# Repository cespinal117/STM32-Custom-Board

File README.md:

# STM32-Custom-Board

This is a board I decided to create to practice my PCB Design skills.  

I chose the STM32 as the main MCU due to me wanting to learn the STM32 platform.

My main motivation for the features of this board is that throughout college I mostly worked on projects involved Servo motors. Instead of having a separate Servo driver board with more wires, I thought it would be nice to have it all embedded into a single PCB that will power and control everything.  
The ESP32 was a last second addition as I thought it would be cool to be able to control the motors wirelessly through a web interface or bluetooth.

# Features
- STM32 MCU as the main processor
- ESP32 for wireless capabitlities
- PCA9685 Servo driver
- Switching between 5V USB or external 5V (prioritizes USB for the MCU if plugged in)

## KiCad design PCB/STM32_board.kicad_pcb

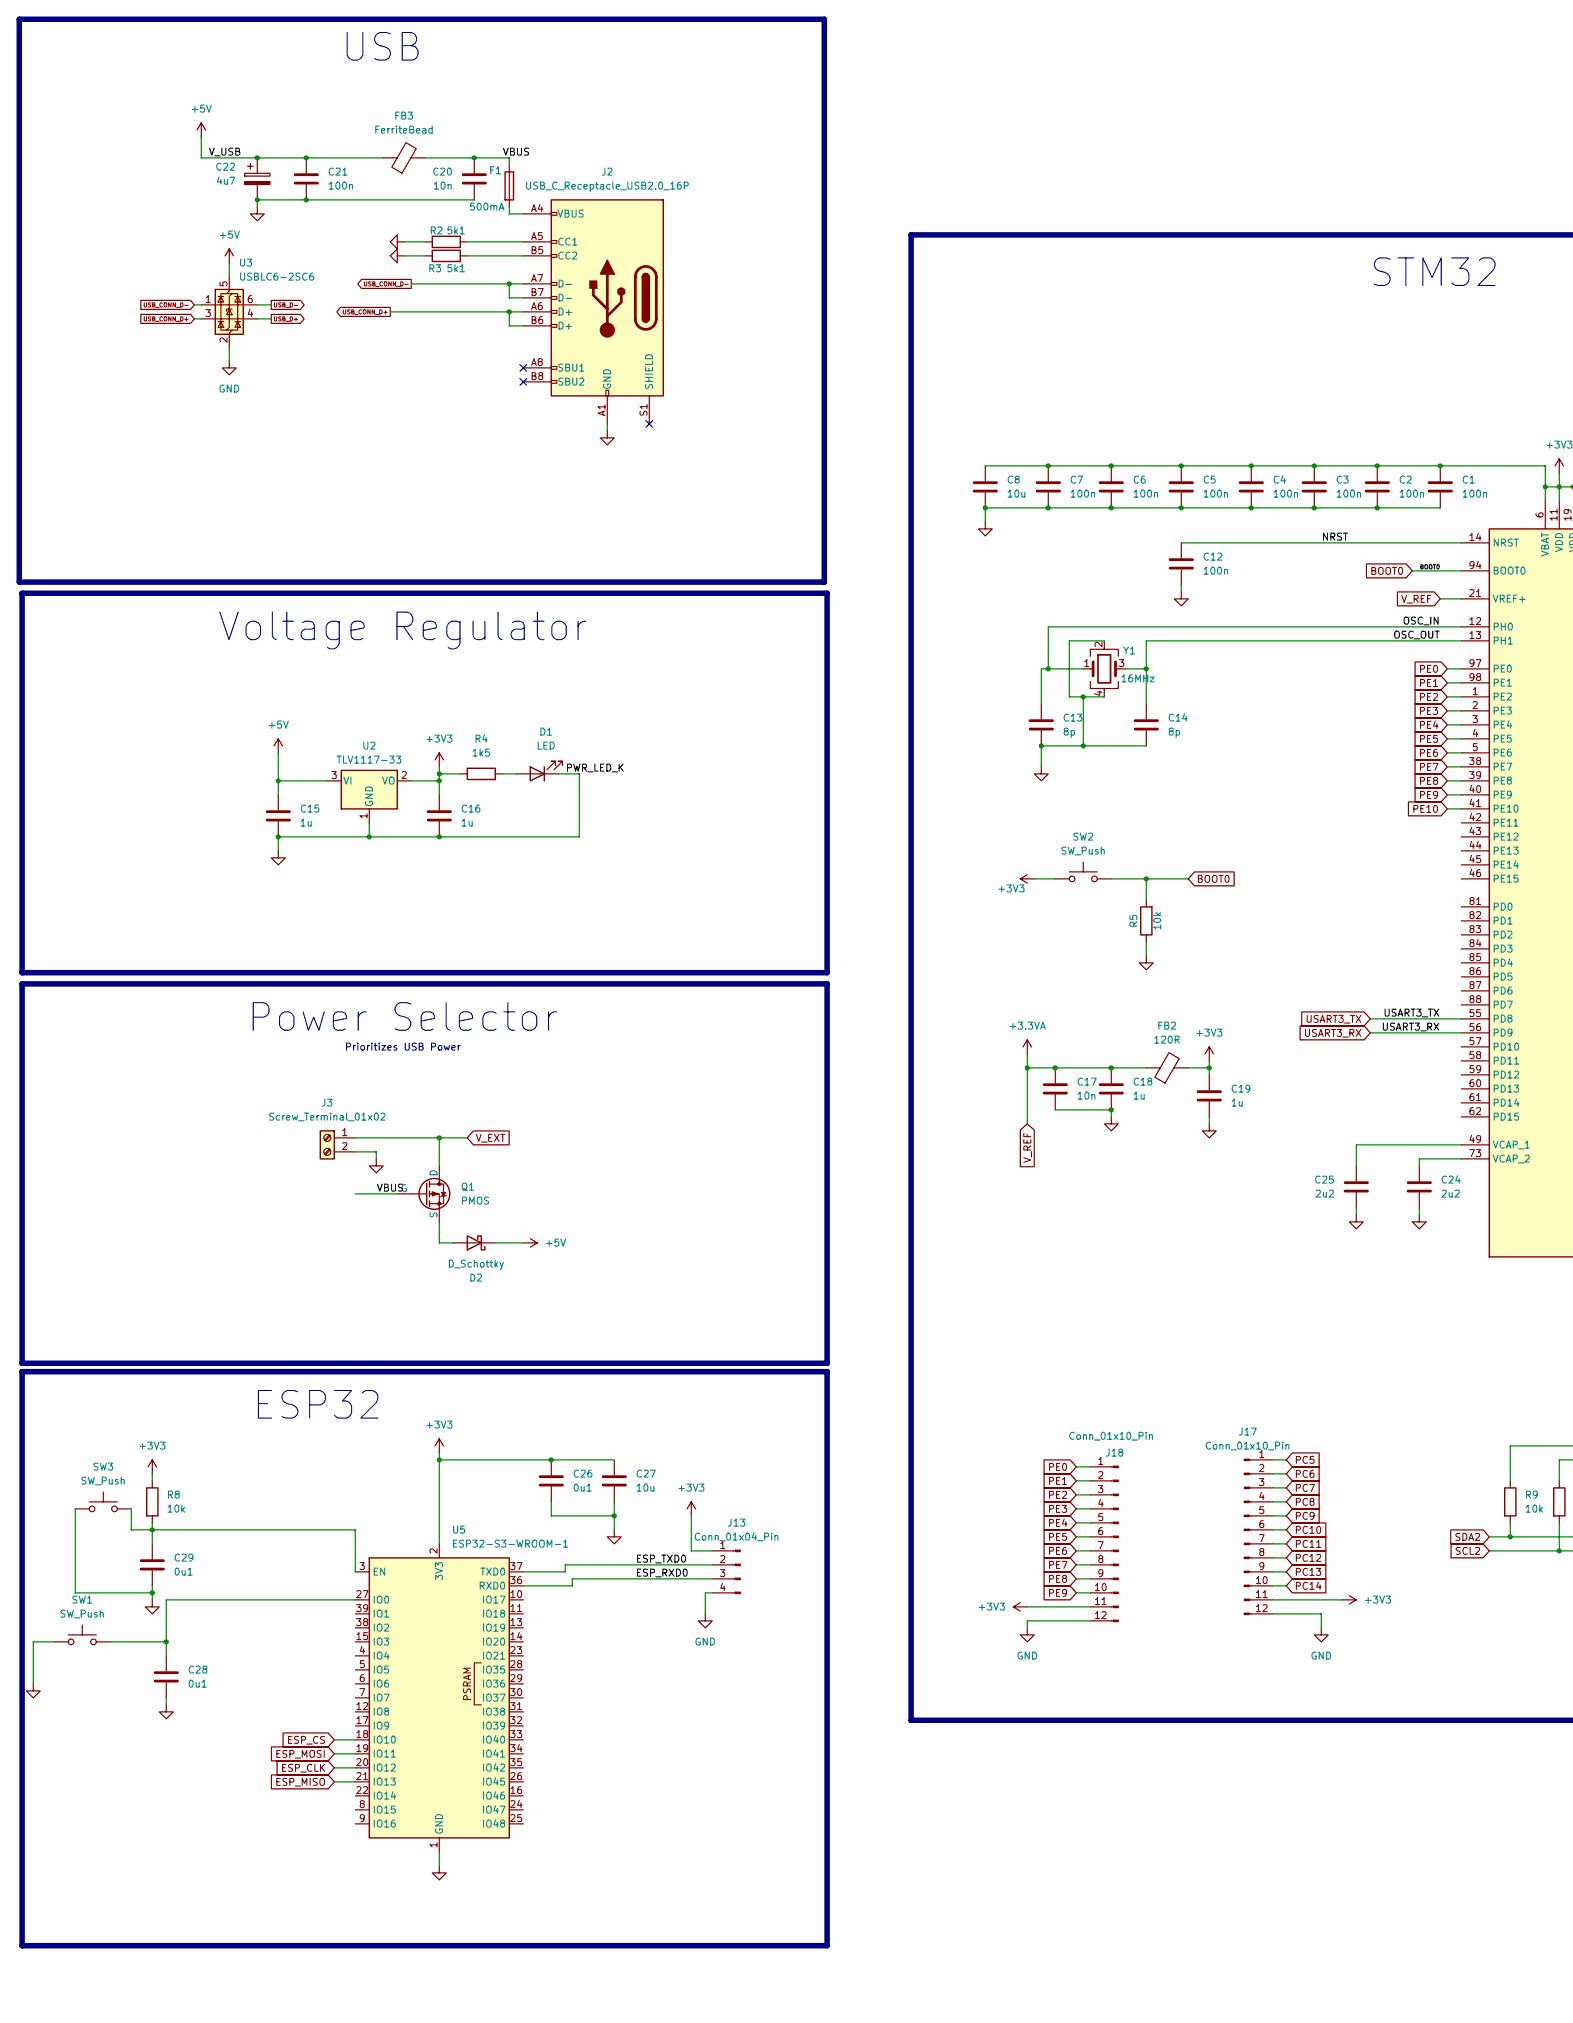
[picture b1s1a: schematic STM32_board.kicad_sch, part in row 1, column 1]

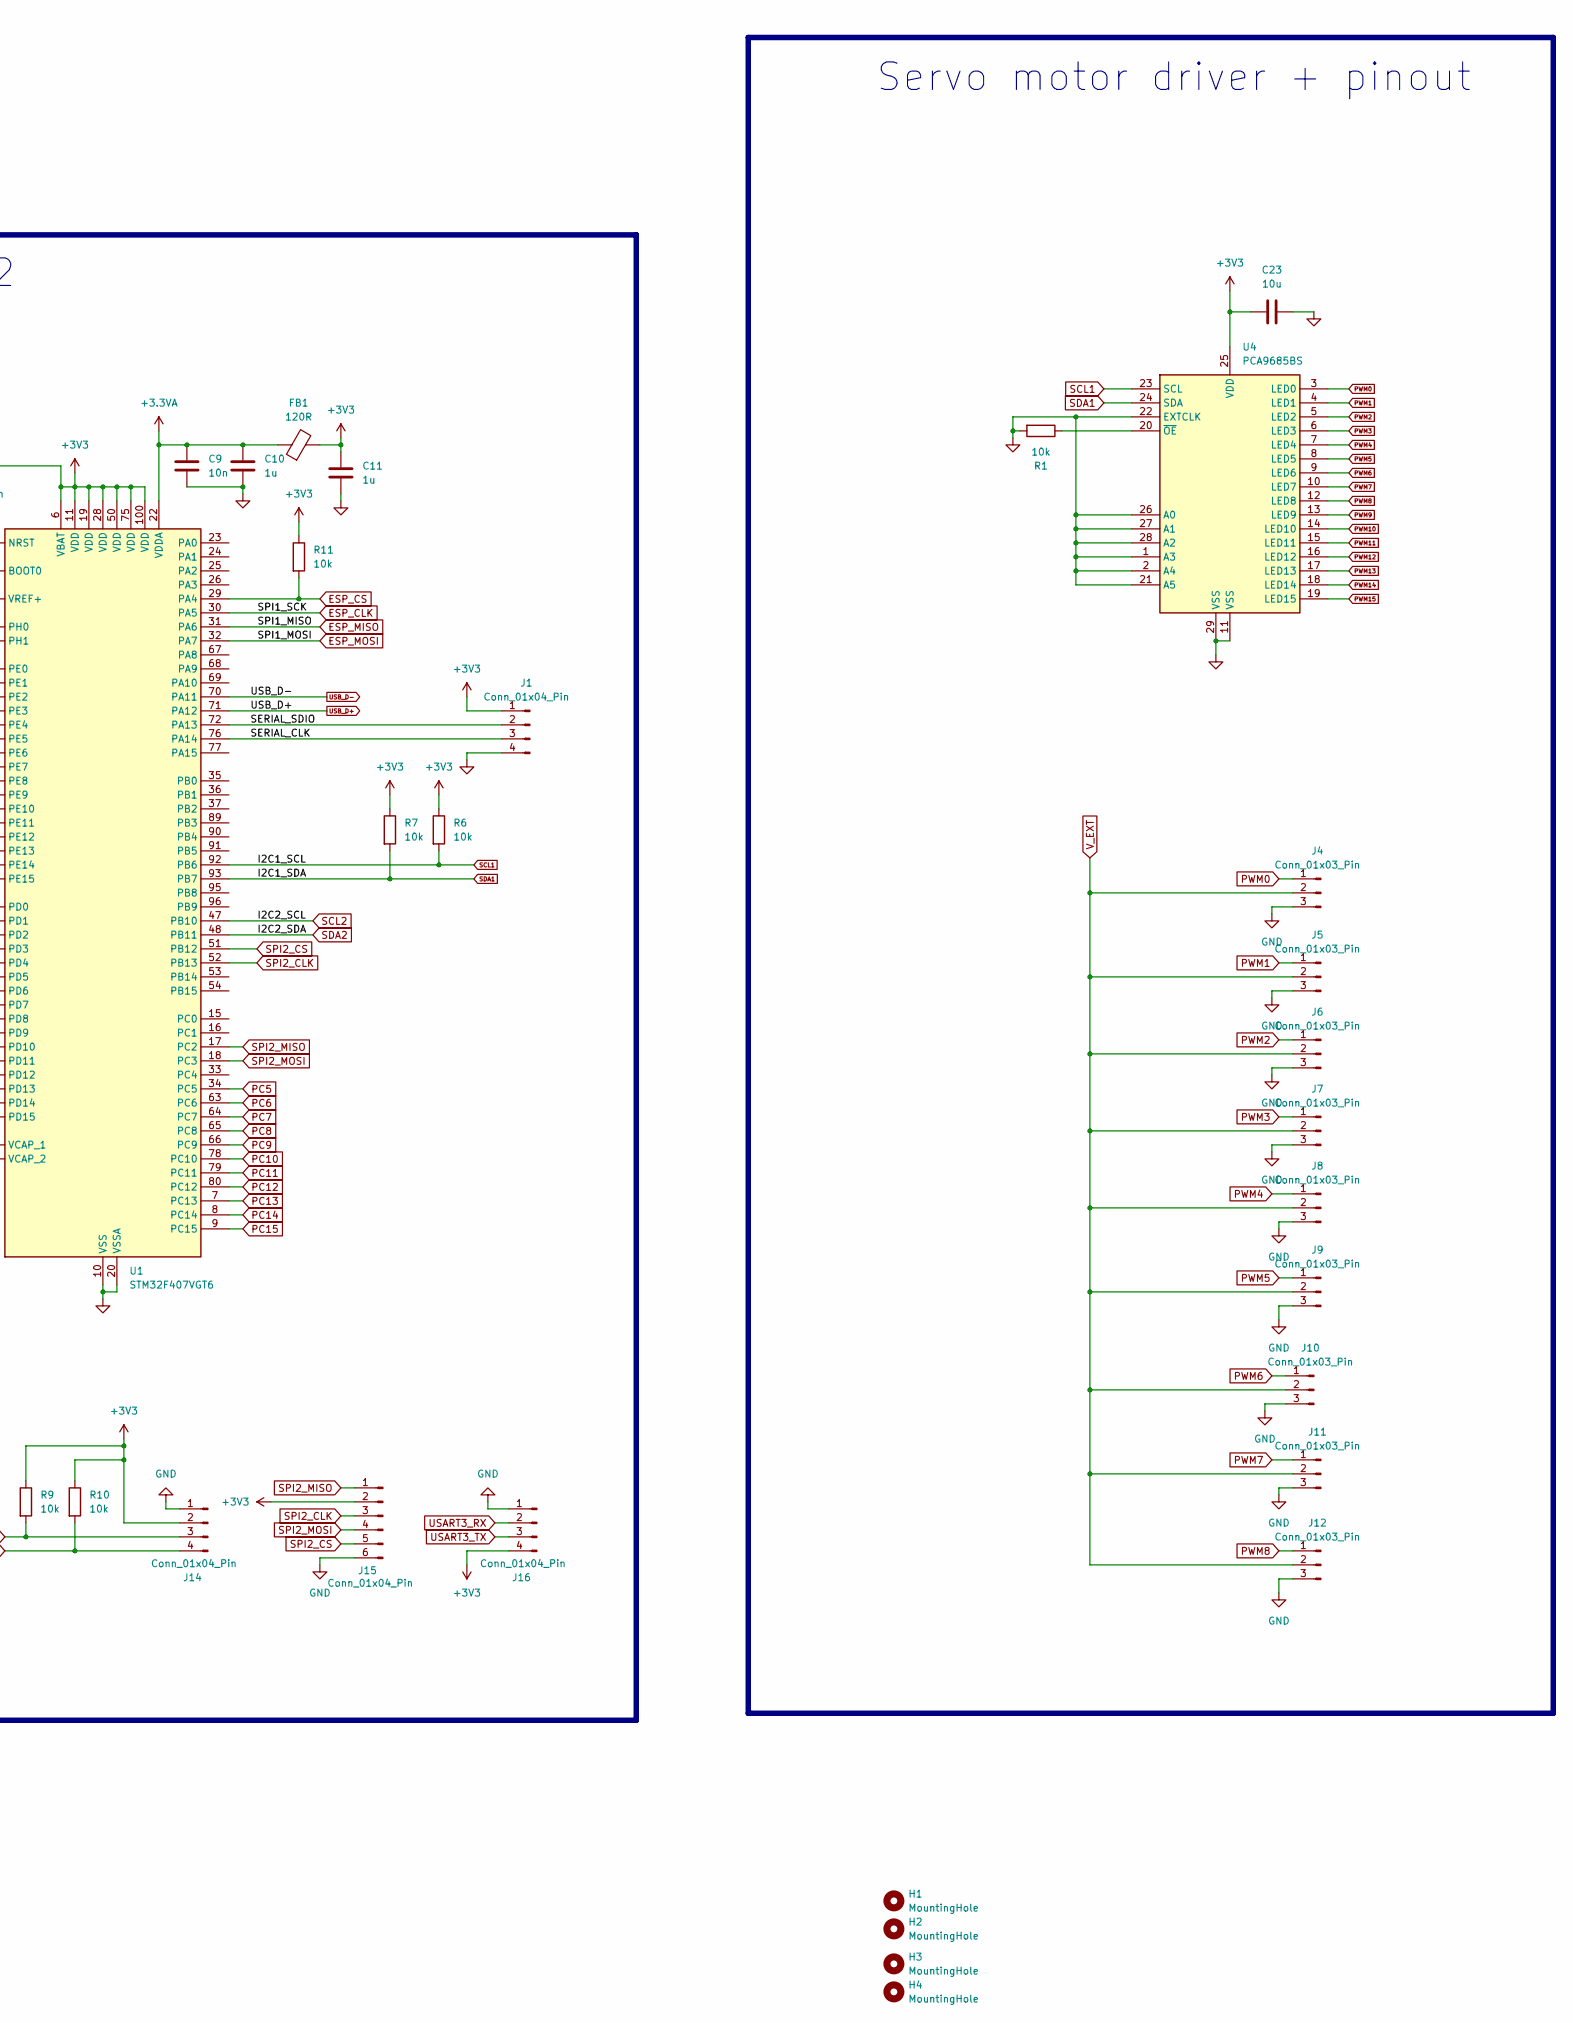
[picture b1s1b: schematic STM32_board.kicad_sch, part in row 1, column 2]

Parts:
C1, C2, C3, C4, C5, C6, C7, C12, C21: 100n; C_0603_1608Metric; Part Number 1276-1000-2-ND
C8, C23, C27: 10u; C_0805_2012Metric; Part Number 1276-1096-2-ND
C9, C17, C20: 10n; C_0402_1005Metric; Part Number 1276-1028-2-ND
C10, C11, C15, C16, C18, C19: 1u; C_0402_1005Metric; Part Number 1276-1067-2-ND
C13, C14: 8p; C_0402_1005Metric; Part Number 1276-CL05C080DB51PNCTR-ND
C22: 4u7; CP_Elec_4x5.7; Part Number 732-8258-2-ND
C24, C25: 2u2; C_0603_1608Metric; Part Number 1276-1040-2-ND
C26, C28, C29: 0u1; C_0603_1608Metric; Part Number 1276-1000-2-ND
D1: LED; LED_0201_0603Metric; Part Number 160-1446-2-ND
D2: D_Schottky; D_SOD-123; Part Number 1N5819HW-FDITR-ND
F1: 500mA; Fuse_1812_4532Metric; Part Number MF-MSMF050-2TR-ND
FB1, FB2: 120R; L_0603_1608Metric; Part Number 490-3996-2-ND
FB3: FerriteBead; L_0603_1608Metric; Part Number 541-2604-2-ND
H1, H2, H3, H4: MountingHole; MountingHole_2.2mm_M2
J1, J13: Conn_01x04_Pin; PinHeader_1x04_P2.54mm_Vertical
J2: USB_C_Receptacle_USB2.0_16P; USB_C_Receptacle_GCT_USB4085; Part Number 2073-USB4085-GF-ATR-ND
J3: Screw_Terminal_01x02; TerminalBlock_Phoenix_MKDS-1,5-2-5.08_1x02_P5.08mm_Horizont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; Part Number 277-1247-ND
J4, J5, J6, J7, J8, J9, J10, J11, J12: Conn_01x03_Pin; PinHeader_1x03_P2.54mm_Vertical
J14, J16: Conn_01x04_Pin; JST_GH_SM04B-GHS-TB_1x04-1MP_P1.25mm_Horizontal; Part Number 455-1566-2-ND
J15: Conn_01x04_Pin; JST_GH_SM06B-GHS-TB_1x06-1MP_P1.25mm_Horizontal; Part Number 455-1568-2-ND
J17, J18: Conn_01x10_Pin; PinHeader_1x12_P2.54mm_Vertical
Q1: PMOS; SOT-23; Part Number SSM3J328RLFTR-ND
R1, R5, R6, R7, R8, R9, R10, R11: 10k; R_0402_1005Metric; Part Number 311-10.0KLRTR-ND
R2, R3: 5k1; R_0402_1005Metric; Part Number 311-5.10KLRTR-ND
R4: 1k5; R_0402_1005Metric; Part Number 311-1.50KLRTR-ND
SW1, SW2, SW3: SW_Push; PTS636 SM43 SMTR LFS; Part Number CKN12310-2-ND
U1: STM32F407VGT6; LQFP-100_14x14mm_P0.5mm; Part Number 497-11605-ND
U2: TLV1117-33; SOT-223-3_TabPin2; Part Number 296-28778-2-ND
U3: USBLC6-2SC6; SOT-23-6; Part Number 497-5235-2-ND
U4: PCA9685BS; QFN-28-1EP_6x6mm_P0.65mm_EP4.25x4.25mm; Part Number 568-5305-2-ND
U5: ESP32-S3-WROOM-1; Part Number 1965-ESP32-S3-WROOM-1-N8TR-ND
Y1: 16MHz; Crystal_SMD_3225-4Pin_3.2x2.5mm_HandSoldering; Part Number SER4069TR-ND

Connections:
+3V3: C1.1, C2.1, C3.1, C4.1, C5.1, C6.1, C7.1, C8.1, C11.1, C16.1, C19.1, C23.1, C26.1, C27.1, FB1.2, FB2.2, J1.1, J13.1, J14.2, J15.2, J16.4, J17.11, J18.11, R4.1, R6.1, R7.1, R8.1, R9.1, R10.1, R11.1, SW2.1, U1.6 (VBAT), U1.11 (VDD), U1.19 (VDD), U1.28 (VDD), U1.50 (VDD), U1.75 (VDD), U1.100 (VDD), U2.2 (VO), U4.25 (VDD), U5.2 (3V3)
+5V: C15.1, C21.1, C22.1, D2.1 (K), FB3.1, U2.3 (VI), U3.5 (VBUS)
/ESP_RXD0: J13.3, U5.36 (RXD0)
/ESP_TXD0: J13.2, U5.37 (TXD0)
/NRST: C12.1, U1.14 (NRST)
/OSC_IN: C13.1, U1.12 (PH0), Y1.1
/OSC_OUT: C14.1, U1.13 (PH1), Y1.3
/SERIAL_CLK: J1.3, U1.76 (PA14)
/SERIAL_SDIO: J1.2, U1.72 (PA13)
/VBUS: C20.1, F1.1, FB3.2, Q1.2 (G)
BOOT0: R5.2, SW2.2, U1.94 (BOOT0)
ESP_CLK: U1.30 (PA5), U5.20 (IO12)
ESP_CS: R11.2, U1.29 (PA4), U5.18 (IO10)
ESP_MISO: U1.31 (PA6), U5.21 (IO13)
ESP_MOSI: U1.32 (PA7), U5.19 (IO11)
GND: C1.2, C2.2, C3.2, C4.2, C5.2, C6.2, C7.2, C8.2, C9.2, C10.2, C11.2, C12.2, C13.2, C14.2, C15.2, C16.2, C17.2, C18.2, C19.2, C20.2, C21.2, C22.2, C23.2, C24.2, C25.2, C26.2, C27.2, C28.2, C29.1, D1.1 (K), J1.4, J2.A1 (GND), J2.A12 (GND), J2.B1 (GND), J2.B12 (GND), J3.2, J4.3, J5.3, J6.3, J7.3, J8.3, J9.3, J10.3, J11.3, J12.3, J13.4, J14.1, J15.6, J16.1, J17.12, J18.12, R1.2, R2.1, R3.1, R5.1, SW1.1, SW3.1, U1.10 (VSS), U1.20 (VSSA), U1.27 (VSS), U1.74 (VSS), U1.99 (VSS), U2.1 (GND), U3.2 (GND), U4.1 (A3), U4.2 (A4), U4.11 (VSS), U4.21 (A5), U4.22 (EXTCLK), U4.26 (A0), U4.27 (A1), U4.28 (A2), U4.29 (VSS), U5.1 (GND), U5.40 (GND), U5.41 (GND), Y1.2, Y1.4
unnamed: D1.2 (A), R4.2
unnamed: D2.2 (A), Q1.3 (S)
unnamed: F1.2, J2.A4 (VBUS), J2.A9 (VBUS), J2.B4 (VBUS), J2.B9 (VBUS)
unnamed: J2.A5 (CC1), R2.2
unnamed: J2.B5 (CC2), R3.2
unnamed: C25.1, U1.49 (VCAP_1)
unnamed: C24.1, U1.73 (VCAP_2)
unnamed: R1.1, U4.20 (~OE)
unnamed: C29.2, R8.2, SW3.2, U5.3 (EN)
unnamed: C28.1, SW1.2, U5.27 (IO0)
PC5: J17.1, U1.34 (PC5)
PC6: J17.2, U1.63 (PC6)
PC7: J17.3, U1.64 (PC7)
PC8: J17.4, U1.65 (PC8)
PC9: J17.5, U1.66 (PC9)
PC10: J17.6, U1.78 (PC10)
PC11: J17.7, U1.79 (PC11)
PC12: J17.8, U1.80 (PC12)
PC13: J17.9, U1.7 (PC13)
PC14: J17.10, U1.8 (PC14)
PC15: U1.9 (PC15)
PE0: J18.1, U1.97 (PE0)
PE1: J18.2, U1.98 (PE1)
PE2: J18.3, U1.1 (PE2)
PE3: J18.4, U1.2 (PE3)
PE4: J18.5, U1.3 (PE4)
PE5: J18.6, U1.4 (PE5)
PE6: J18.7, U1.5 (PE6)
PE7: J18.8, U1.38 (PE7)
PE8: J18.9, U1.39 (PE8)
PE9: J18.10, U1.40 (PE9)
PE10: U1.41 (PE10)
PWM0: J4.1, U4.3 (LED0)
PWM1: J5.1, U4.4 (LED1)
PWM2: J6.1, U4.5 (LED2)
PWM3: J7.1, U4.6 (LED3)
PWM4: J8.1, U4.7 (LED4)
PWM5: J9.1, U4.8 (LED5)
PWM6: J10.1, U4.9 (LED6)
PWM7: J11.1, U4.10 (LED7)
PWM8: J12.1, U4.12 (LED8)
PWM9: U4.13 (LED9)
PWM10: U4.14 (LED10)
PWM11: U4.15 (LED11)
PWM12: U4.16 (LED12)
PWM13: U4.17 (LED13)
PWM14: U4.18 (LED14)
PWM15: U4.19 (LED15)
SCL1: R6.2, U1.92 (PB6), U4.23 (SCL)
SCL2: J14.4, R10.2, U1.47 (PB10)
SDA1: R7.2, U1.93 (PB7), U4.24 (SDA)
SDA2: J14.3, R9.2, U1.48 (PB11)
SPI2_CLK: J15.3, U1.52 (PB13)
SPI2_CS: J15.5, U1.51 (PB12)
SPI2_MISO: J15.1, U1.17 (PC2)
SPI2_MOSI: J15.4, U1.18 (PC3)
USART3_RX: J16.2, U1.56 (PD9)
USART3_TX: J16.3, U1.55 (PD8)
USB_CONN_D+: J2.A6 (D+), J2.B6 (D+), U3.3 (I/O2)
USB_CONN_D-: J2.A7 (D-), J2.B7 (D-), U3.1 (I/O1)
USB_D+: U1.71 (PA12), U3.4 (I/O2)
USB_D-: U1.70 (PA11), U3.6 (I/O1)
V_EXT: J3.1, J4.2, J5.2, J6.2, J7.2, J8.2, J9.2, J10.2, J11.2, J12.2, Q1.1 (D)
V_REF: C9.1, C10.1, C17.1, C18.1, FB1.1, FB2.1, U1.21 (VREF+), U1.22 (VDDA)

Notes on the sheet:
ESP32
STM32
Servo motor driver + pinout
Power Selector
Voltage Regulator
Prioritizes USB Power
USB

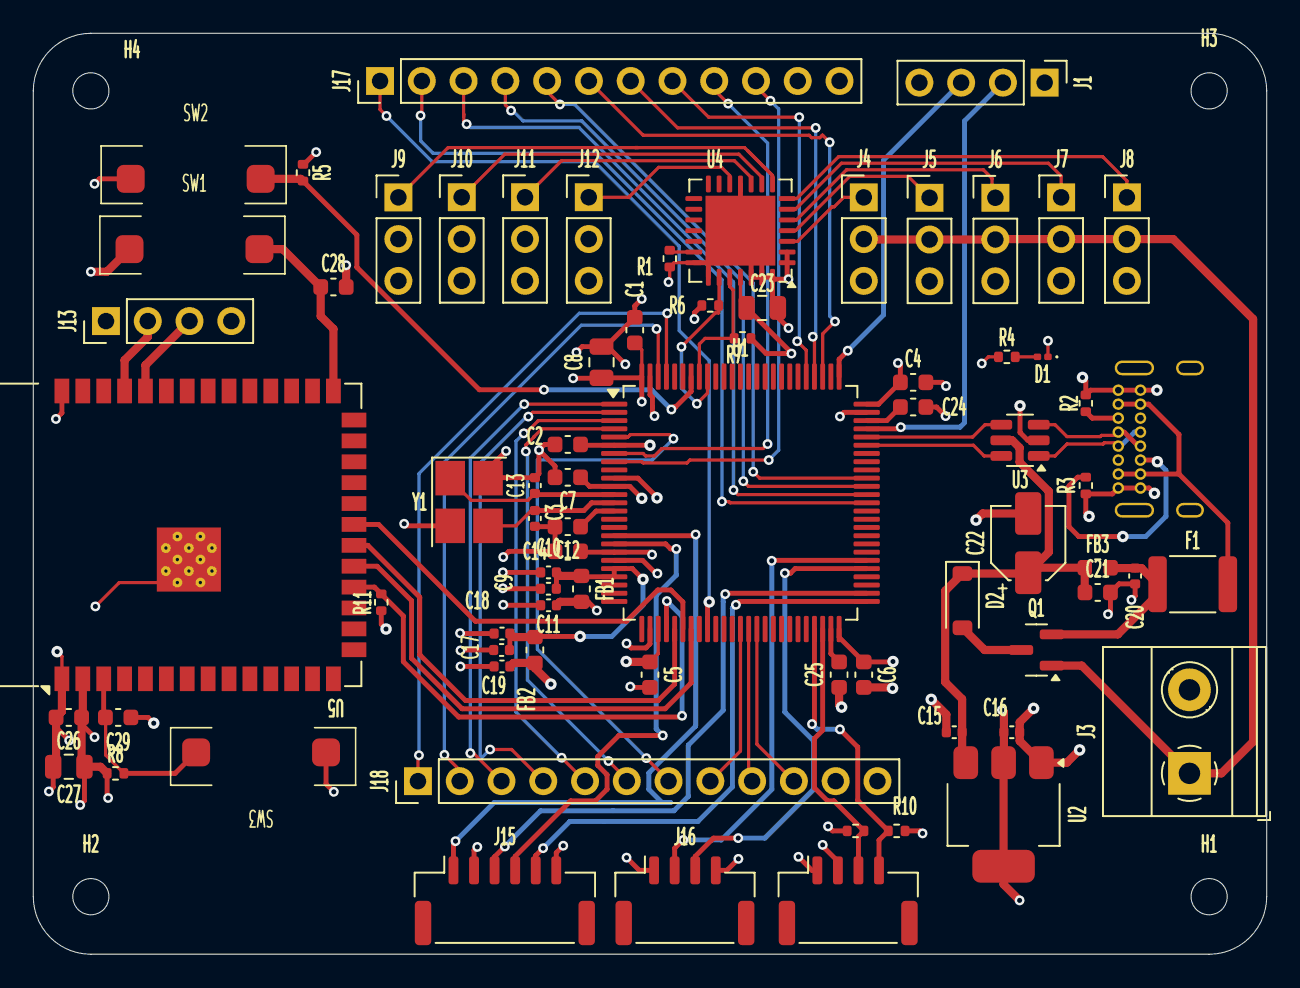
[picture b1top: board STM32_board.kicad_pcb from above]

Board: 4 copper layers, 75.0 x 56.0 mm, 78 parts (1 on the bottom side), 71 nets.

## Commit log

2025-12-03 added pcb files
